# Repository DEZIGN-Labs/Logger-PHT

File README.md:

### Design Files

- **Tool:** Autodesk Eagle
- **Schematic:** [View schematic](hardware/PHT_logger.sch)
- **PCB Layout:** [View PCB](hardware/PHT_logger.brd) *(if you have it)*
- **BOM:** [View BOM](hardware/bom/PHT_logger-bom.csv)

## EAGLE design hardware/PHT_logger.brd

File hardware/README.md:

# Hardware Documentation

## PCB Design

### Design Tool
- **Software:** EAGLE
- **Layers:** 4-layer PCB
- **Dimensions:** 50mm x 45mm
- **Thickness:** 1.6mm

### Manufacturing

**Recommended Manufacturer:** JLCPCB

**Specifications:**
- Base Material: FR-4 TG 130-140
- Layers: 4
- PCB Thickness: 1.6mm
- Copper Weight: 1oz
- Surface Finish: HASL (Lead-Free) or ENIG
- Min Track/Spacing: 6/6 mil
- Min Hole Size: 0.3mm

**Cost Estimate:** ~$2 per board (5 boards + shipping)

### Assembly

See [../docs/assembly-guide.md](../docs/assembly-guide.md) for detailed instructions.

**Difficulty:** Intermediate
- SMD soldering required
- Hot air station recommended for QFN packages
- Can be hand-soldered with patience

### Main Components
- ESP32-C3-MINI-1
- BME688 environmental sensor
- TP4056 charging controller
- MAX17048 fuel gauge
- 18650 battery holder

### Bill of Materials

See [bom/basement-sensor-bom.csv](bom/basement-sensor-bom.csv)

**Total Cost per Unit:** ~$15-20 (excluding battery and tools)

### Schematic Overview

[Add schematic image or PDF link here]

### PCB Layout

[Add PCB render or layout image here]

## Design Files

### Eagle Project
- **Schematic:** `PHT_logger.sch`
- **Board:** `PHT_logger.brd` *(if applicable)*
- **Design Tool:** Autodesk Eagle

### Opening Files

1. Download and install [Autodesk Eagle](https://www.autodesk.com/products/eagle)
2. Open the schematic: `File → Open → PHT_logger.sch`
3. Open the board: `File → Open → PHT_logger.brd`

## Version History

### v1.0 (Current)
- Initial release
- TP4056 charging circuit
- ESP32-C3-MINI-1 module
- BME688 sensor
- MAX17048 fuel gauge

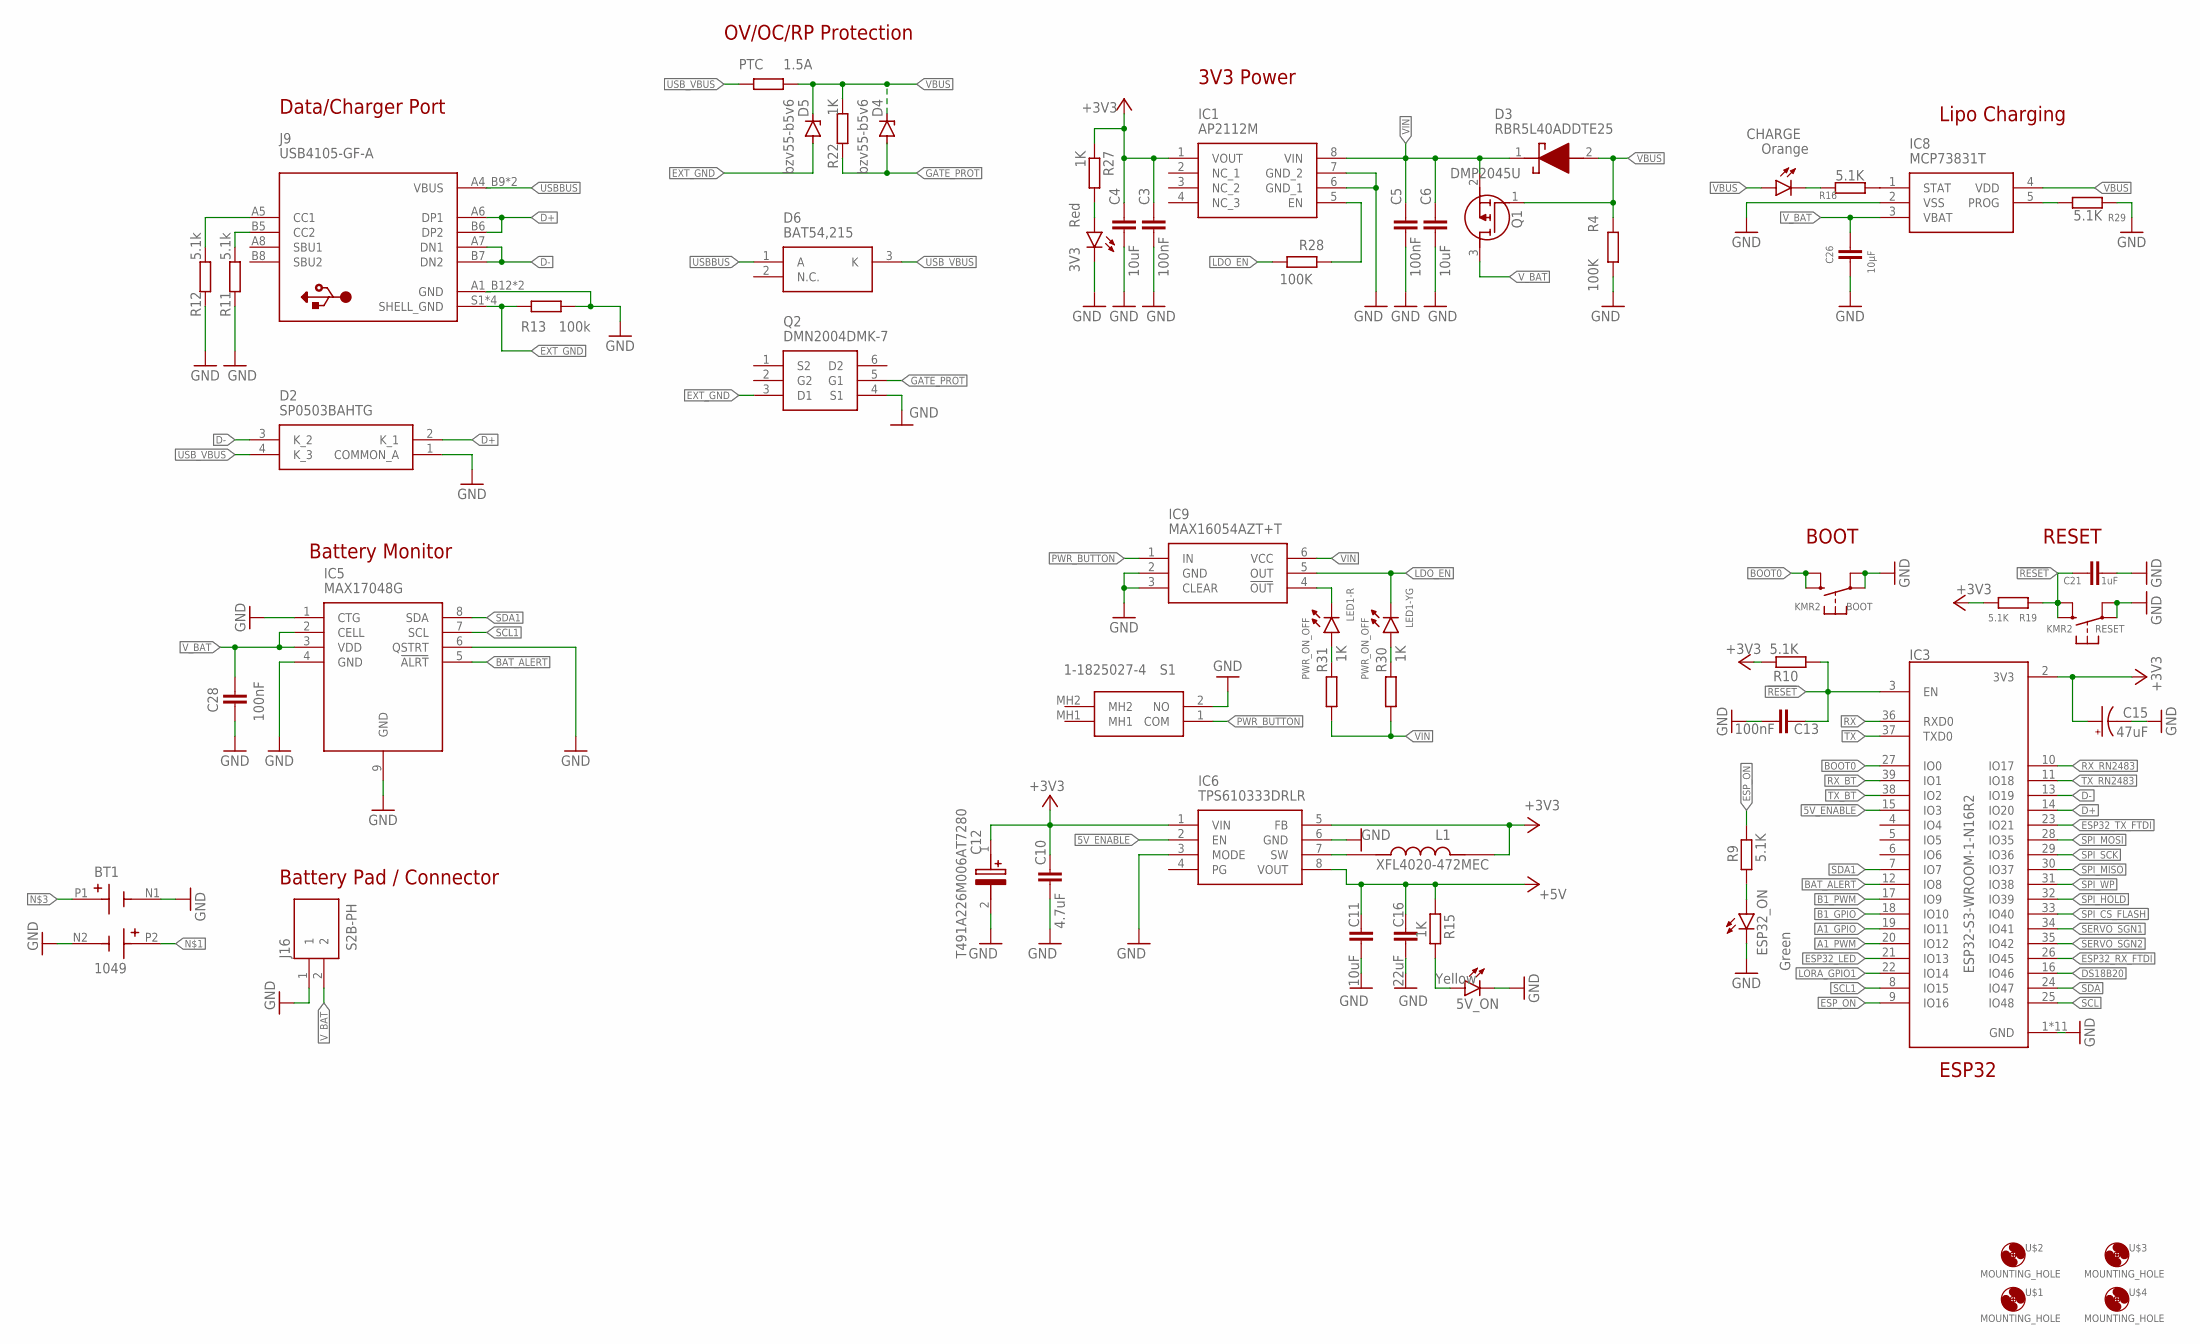
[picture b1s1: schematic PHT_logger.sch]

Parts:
3V3: Red; CHIPLED_0805
5V_ON: Yellow; CHIPLED_0805
BOOT: KMR2; BTN_KMR2_4.6X2.8
BT1: 1049; BAT_1049
C3, C5, C13, C28: 100nF; C0603
C4, C6: 10uF; C0603
C10: 4.7uF; C0805
C11: 10uF; C0805
C12: T491A226M006AT7280; T491A
C15: 47uF; CAPMP6032X250N
C16: 22uF; C0805
C21: 1uF; C0603
C26: 10µF; C0603K
CHARGE: Orange; CHIPLED_0805
D2: SP0503BAHTG
D3: RBR5L40ADDTE25; DIOM5026X220N
D4, D5: bzv55-b5v6; SOD80C
D6: BAT54,215; SOT95P230X110-3N
ESP32_ON: Green; CHIPLED_0805
IC1: AP2112M; SOIC127P600X170-8N
IC3: ESP32-S3-WROOM-1-N16R2; XCVR_ESP32-S3-WROOM-1-N16R2
IC5: MAX17048G; SON50P200X200X80-9N
IC6: TPS610333DRLR; SOTFL50P160X60-8N
IC8: MCP73831T; SOT95P270X145-5N
IC9: MAX16054AZT+T; SOT95P275X110-6N
J9: USB4105-GF-A; GCT_USB4105-GF-A
J16: S2B-PH; JST_S2B-PH-K-S(LF)(SN)
L1: XFL4020-472MEC; IND_XFL4020-472MEC
LED1: PWR_ON_OFF; 3216(1206)-4
PTC: 1.5A; R2512
Q1: DMP2045U; SOT96P240X110-3N
Q2: DMN2004DMK-7; SOT95P285X145-6N
R4, R28: 100K; R0603
R9, R10, R16, R19, R29: 5.1K; R0603
R11, R12: 5.1k; R0603
R13: 100k; R0603
R15, R22, R27, R30, R31: 1K; R0603
RESET: KMR2; BTN_KMR2_4.6X2.8
S1: 1-1825027-4; 118250274
U$1, U$2, U$3, U$4: MOUNTING_HOLE

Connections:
5V_ENABLE: IC3.15 (IO3), IC6.2 (EN)
!RESET: C13.1, C21.1, IC3.3 (EN), R10.1, R19.1, RESET.B (S), RESET.B' (S1)
+3V3: C3.2, C4.2, C10.2, C12.1 (+), C15.1 (+), IC1.1 (VOUT), IC3.2 (3V3), IC6.1 (VIN), IC6.5 (FB), L1.2, R10.2, R19.2, R27.1
+5V: C11.2, C16.2, IC6.8 (VOUT), R15.1
A1_GPIO: IC3.19 (IO11)
A1_PWM: IC3.20 (IO12)
B1_GPIO: IC3.18 (IO10)
B1_PWM: IC3.17 (IO9)
BAT_ALERT: IC3.12 (IO8), IC5.5 (!ALRT)
BOOT0: BOOT.B (S), BOOT.B' (S1), IC3.27 (IO0)
D+: D2.2 (K_1), IC3.14 (IO20), J9.A6 (DP1), J9.B6 (DP2)
D-: D2.3 (K_2), IC3.13 (IO19), J9.A7 (DN1), J9.B7 (DN2)
DS18B20: IC3.16 (IO46)
ESP32_LED: IC3.21 (IO13)
ESP32_RX_FTDI: IC3.26 (IO45)
ESP32_TX_FTDI: IC3.23 (IO21)
ESP_ON: IC3.9 (IO16), R9.2
EXT_GND: D5.A, J9.S1 (SHELL_GND), J9.S2 (SHELL_GND), J9.S3 (SHELL_GND), J9.S4 (SHELL_GND), Q2.3 (D1), R13.2
GATE_PROT: D4.A, Q2.5 (G1), R22.1
GND: 3V3.C, 5V_ON.C, BOOT.A, BOOT.A' (P1), BT1.N1 (NEG1), BT1.N2 (NEG2), C3.1, C4.1, C5.1, C6.1, C10.1, C11.1, C12.2 (-), C13.2, C15.2 (-), C16.1, C21.2, C26.2, C28.2, D2.1 (COMMON_A), ESP32_ON.C, IC1.6 (GND_1), IC1.7 (GND_2), IC3.1 (GND), IC3.40 (GND), IC3.41_1 (GND), IC3.41_2 (GND), IC3.41_3 (GND), IC3.41_4 (GND), IC3.41_5 (GND), IC3.41_6 (GND), IC3.41_7 (GND), IC3.41_8 (GND), IC3.41_9 (GND), IC5.1 (CTG), IC5.4 (GND), IC5.6 (QSTRT), IC5.9 (GND), IC6.3 (MODE), IC6.6 (GND), IC8.2 (VSS), IC9.2 (GND), IC9.3 (CLEAR), J9.A1_B12 (GND), J9.B1_A12 (GND), J16.1, Q2.4 (S1), R4.2, R11.1, R12.1, R13.1, R29.1, RESET.A, RESET.A' (P1), S1.2 (NO)
LDO_EN: IC9.5 (OUT), LED1.3 (C), R28.1
LORA_GPIO1: IC3.22 (IO14)
unnamed: ESP32_ON.A, R9.1
unnamed: IC6.7 (SW), L1.1
unnamed: 5V_ON.A, R15.2
unnamed: CHARGE.C, R16.1
unnamed: IC9.4 (!OUT), LED1.1 (C)
unnamed: IC1.5 (EN), R28.2
unnamed: LED1.4 (A), R30.2
unnamed: LED1.2 (A), R31.2
unnamed: J9.B5 (CC2), R11.2
unnamed: IC8.1 (STAT), R16.2
unnamed: IC8.5 (PROG), R29.2
unnamed: J9.A5 (CC1), R12.2
unnamed: 3V3.A, R27.2
PWR_BUTTON: IC9.1 (IN), S1.1 (COM)
RX: IC3.36 (RXD0)
RX_BT: IC3.39 (IO1)
RX_RN2483: IC3.10 (IO17)
SCL: IC3.25 (IO48)
SCL1: IC3.8 (IO15), IC5.7 (SCL)
SDA: IC3.24 (IO47)
SDA1: IC3.7 (IO7), IC5.8 (SDA)
SERVO_SGN1: IC3.34 (IO41)
SERVO_SGN2: IC3.35 (IO42)
SPI_CS_FLASH: IC3.33 (IO40)
SPI_HOLD: IC3.32 (IO39)
SPI_MISO: IC3.30 (IO37)
SPI_MOSI: IC3.28 (IO35)
SPI_SCK: IC3.29 (IO36)
SPI_WP: IC3.31 (IO38)
TX: IC3.37 (TXD0)
TX_BT: IC3.38 (IO2)
TX_RN2483: IC3.11 (IO18)
USBBUS: D6.1 (A), J9.A4_B9 (VBUS), J9.B4_A9 (VBUS)
USB_VBUS: D2.4 (K_3), D6.3 (K), PTC.1
VBUS: CHARGE.A, D3.2 (A), D4.C, D5.C, IC8.4 (VDD), PTC.2, Q1.1 (G), R4.1, R22.2
VIN: C5.2, C6.2, D3.1 (K), IC1.8 (VIN), IC9.6 (VCC), Q1.2 (S), R30.1, R31.1
V_BAT: C26.1, C28.1, IC5.2 (CELL), IC5.3 (VDD), IC8.3 (VBAT), J16.2, Q1.3 (D)

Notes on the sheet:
ESP32
RESET
BOOT
3V3 Power
Battery Pad / Connector
Battery Monitor
Lipo Charging
Data/Charger Port
OV/OC/RP Protection

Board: 4 copper layers, 58 parts (1 on the bottom side), 34 nets, no tracks yet.

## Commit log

2025-11-16 Initial commit: ESP32-C3 basement sensor with Eagle design
2025-11-16 Updated hardware README.md
2025-11-16 ESP32 updated on schematics
2025-11-19 Powe components updated on schematics

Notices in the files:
parts and their libraries:
microbuilder: This work is placed in the public domain, and may be freely used for commercial and non-commercial work with the following conditions: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
